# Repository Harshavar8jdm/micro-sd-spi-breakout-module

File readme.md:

# 3.3V MicroSD Card SPI Breakout Board

A compact, high-performance, 2-layer **MicroSD Card Breakout Board** designed in KiCad for embedded microcontrollers using the **SPI (Serial Peripheral Interface)** bus.

Designed specifically for 3.3V native logic ecosystems (STM32, ESP32, RP2040, SAMD, Nordic, etc.), this module provides clean power decoupling, signal pull-ups, and a low-EMI ground plane layout.

---

## Board Renders

| Top View | Bottom View |
| :---: | :---: |
|  |  |

---

## Key Features

* **Native 3.3V Operation:** Designed without slow active/passive level shifters, maximizing SPI bus speeds (up to 25 MHz) with zero signal propagation delay.
* **Transient Power Decoupling:** Dedicated 10 uF bulk ceramic cap (C1) and 100 nF high-frequency ceramic cap (C2) positioned directly adjacent to the SD socket's VDD pin (Pin 4) to handle flash memory write current spikes (up to 200 mA).
* **Bus Stability:** Integrated 10k Ohm pull-up resistors on signal lines to prevent floating inputs and accidental bus writes during microcontroller startup/reset.
* **Card Detection:** Mechanically broken-out Card Detect (CD_DET) line to trigger hardware interrupts on card insertion/removal.
* **Optimized 2-Layer Signal Integrity:** Signal routing optimized for continuous return paths over an unbroken bottom Ground plane, minimizing EMI and clock ringing.
* **Standard 2.54mm Header:** 1x7 pin header footprint for breadboard prototyping or jumper wiring.

---

## Schematic & Layout

### Schematic

### PCB Layout

---

## Bill of Materials (BOM)

| Reference | Quantity | Value / Part | Footprint / Package | Description |
| :--- | :---: | :--- | :--- | :--- |
| **U1** | 1 | `TF_SMD_TF-PUSH` | MicroSD Push-Push Connector | Surface Mount TF/MicroSD Socket |
| **J1** | 1 | `Conn_01x07_Pin` | PinHeader 1x07, P2.54mm, Vertical | 0.1 inch Pitch Male Pin Header |
| **C1** | 1 | 10 uF | Ceramic Cap, 0805 | Bulk Power Decoupling |
| **C2** | 1 | 100 nF | Ceramic Cap, 0603 | High-Frequency Decoupling |
| **R1, R2** | 2 | 10k Ohm | Resistor, 0603 | Signal Pull-Up Resistors |

---

## Software Integration & Bring-Up Guide

### 1. SPI Clock Speed Stages
When writing software/drivers for SD cards via SPI:
1. **Initialization Phase (100 kHz - 400 kHz):** The SD Card specification requires initial setup (`CMD0`, `CMD8`, `ACMD41`) to be executed at a slow clock speed (<400 kHz) while the card initializes its internal state machine into SPI mode.
2. **Operational Phase (10 MHz - 25 MHz):** Once initialized into SPI mode, increase your MCU's SPI peripheral clock frequency up to **20-25 MHz** for high-throughput block read/write transfers.

### 2. Microcontroller Compatibility Notice
* **Native 3.3V MCUs (STM32, ESP32, RP2040, SAMD):** Connect directly to header pins.
* **5V MCUs (e.g., Classic Arduino Uno R3):** Require external active level shifters (like 74LVC125A) on `SCK`, `MOSI`, and `CS` lines to prevent over-voltage damage to the SD card.

---

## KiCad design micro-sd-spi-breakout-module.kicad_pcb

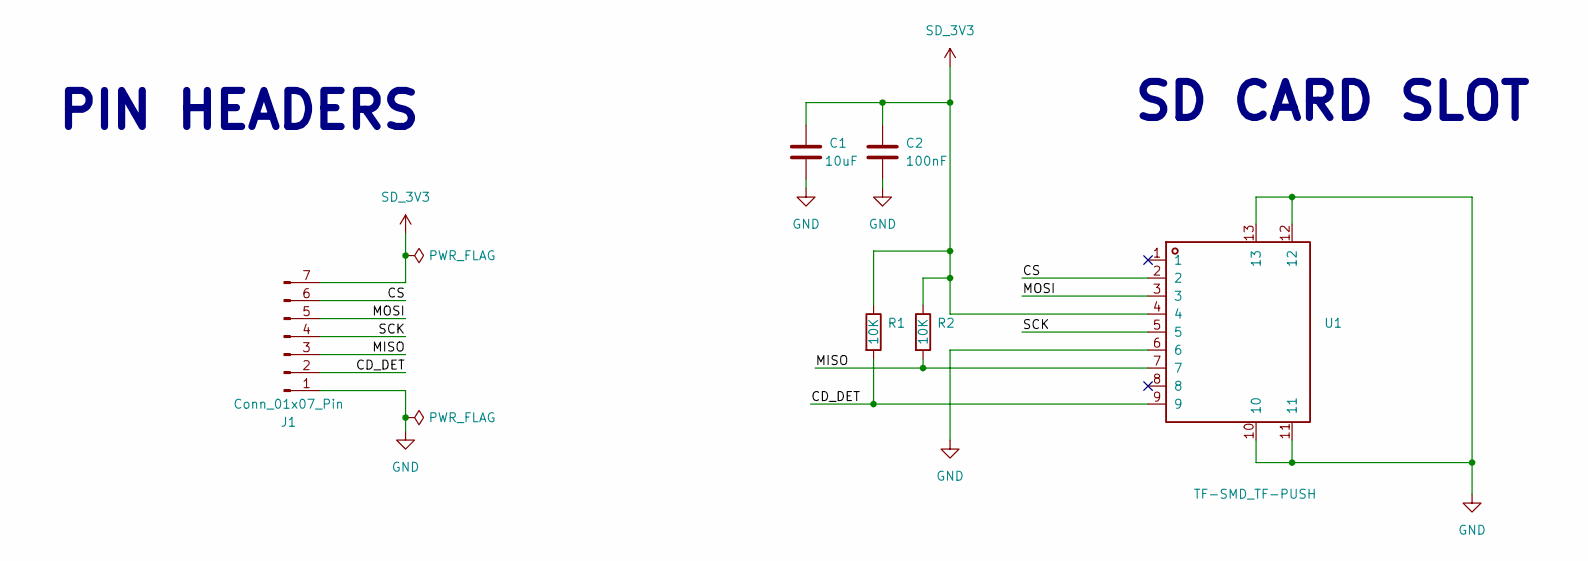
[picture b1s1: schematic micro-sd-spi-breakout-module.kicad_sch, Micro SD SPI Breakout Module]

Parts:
C1: 10uF; C0603_CL10A106KP8NNNC_C19702
C2: 100nF; C0603_CC0603JRX7R9BB104_C91183
J1: Conn_01x07_Pin; PinHeader_1x07_P2.54mm_Horizontal
R1, R2: 10K; R0603_FRC0603F1001TS_C2907002
U1: TF-SMD_TF-PUSH; TF-SMD_TF-PUSH_TF_PUSH_C393941

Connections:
/CD_DET: J1.2, R1.2, U1.9
/CS: J1.6, U1.2
/MISO: J1.3, R2.2, U1.7
/MOSI: J1.5, U1.3
/SCK: J1.4, U1.5
GND: C1.2, C2.2, J1.1, U1.6, U1.10, U1.11, U1.12, U1.13
SD_3V3: C1.1, C2.1, J1.7, R1.1, R2.1, U1.4

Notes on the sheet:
PIN HEADERS
SD CARD SLOT

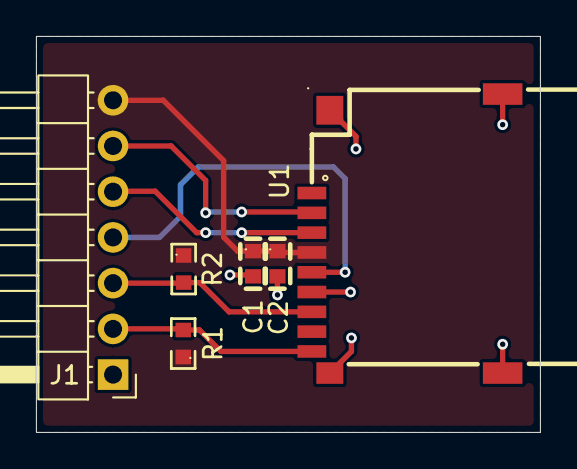
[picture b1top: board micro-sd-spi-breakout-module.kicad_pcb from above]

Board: 2 copper layers, 28.0 x 22.0 mm, 6 parts (0 on the bottom side), 7 nets.
